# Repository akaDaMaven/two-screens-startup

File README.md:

Made and put together by DaMaven.
I'm not an native English speaker so please forgive me my grammar errors.

What does it do: This makes your desired app run on startup on two extended displays with two
 instances of the app each on its own display automaticaly. If you have more displays and want
 that app on all of them, I will show you how.

Use: I've done this for a restaurant that has two touchscreen monitors connected to one server
 (PC) with POS app that needed to be used from different locations without interfering.
 So if you need something like that, there it is.

Follow instuctions bellow:
--------------------------------
1.Download DisplayFusion from official DisplayFusion website (www.displayfusion.com)
	- This alows you to switch the app window inbetween all monitors no matter what side it is set on
	  in windows display settings. DisplayFusion has that on default to "CTRL+WindowsKey+X".

2.Install AutoHotkey_2.0.12_setup.exe OR download from official AutoHotkey website (www.autohotkey.com)
	- This alows the script to use hotkeys ( In our case it is the "CTRL+WindowsKey+X")
	  and convert .ahk file to .exe file. We want to convert .ahk file we create with AutoHotkey to .exe file
	  so we can run it on any PC that doesn't have AutoHotkey installed. To do that, open the Autohotkey Dash
	  and select "Compile". If that doesn't work install Ahk2Exe from Autohotkey folder in
	  "C:\Users\*USERNAME\AppData\Local\Programs\AutoHotkey\UX\install-ahk2exe.ahk". So once in Ahk2Exe is opened
	  in the Source browse path to your "AutoHotkeyScript.ahk" file, go to Base File under Options
	  and select your version of U64 AutoHotkey64.exe, if you have 32 bit system select U32 AutoHotkey32.exe.
	  Now click "Convert". Again you don't have to convert it if you have AutoHotkey installed.

IF you want to configure the hotkeys, edit the AutoHotkeyScript.ahk and go to the first line where it says
 "Send, #^x", search online for Autohotkey's documentation for Autohotkey Version 2.0 or go to
 "www.autohotkey.com/docs/v2/Hotkeys.htm". Once you know the hotkey shortcuts (#,^,!,etc.),
  type it after the "Send, {hotkeys}". Bare in mind that if you download a different version of AutoHotkey
  it does't have to work.

4.Edit the Autorun.ps1
	- First line - Change the path to where you have the application located.
	- Fourth line - (optional) Change the time after the app window moves to second screen.
	- Fifth line - Change the path to where you have the "AutoHotkeyScript.exe" located.

5.Create a shortcut for the "Autorun.ps1". Press "WindowsKey+R" and type in "shell:startup" (this opens Windows
 Startup folder). Copy the "Autorun.ps1" shortcut and copy it to the Windows Startup folder.

That's it!

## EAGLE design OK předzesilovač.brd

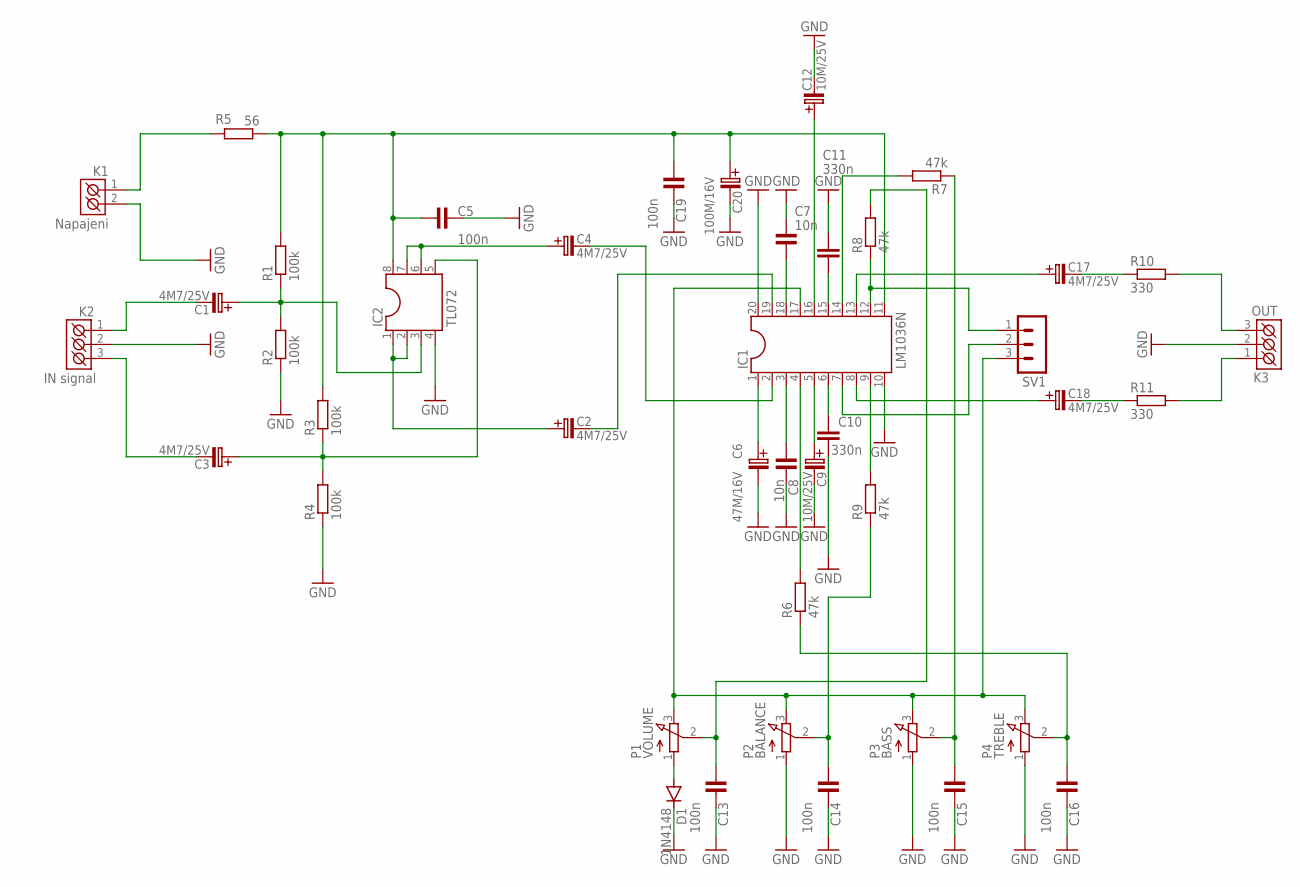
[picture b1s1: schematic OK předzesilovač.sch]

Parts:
C1, C2, C3, C4, C17, C18: 4M7/25V; C_EL_2
C5, C13, C14, C15, C16, C19: 100n; RM5_2,5
C6: 47M/16V; C_EL_2
C7, C8: 10n; RM5_2,5
C9, C12: 10M/25V; C_EL_2,5
C10, C11: 330n; C075-032X103
C20: 100M/16V; C_EL_3,5
D1: 1N4148; DO35-7
IC1: LM1036N; DIL20
IC2: TL072; DIL08
K1: Napajeni; ARK500/2
K2: IN signal; ARK500/3
K3: OUT; ARK500/3
P1: VOLUME; 3RP/1610N
P2: BALANCE; 3RP/1610N
P3: BASS; 3RP/1610N
P4: TREBLE; 3RP/1610N
R1: 100k; 0207/12
R2, R3, R4: 100k; 0204/7
R5: 56; 0204/7
R6, R7, R8, R9: 47k; 0207/12
R10: 330; 0204/7
R11: 330; 0207/12
SV1: MA03-1

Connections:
GND: C5.2, C6.C- (C_EL-), C7.1, C8.2, C9.C- (C_EL-), C10.2, C11.1, C12.C- (C_EL-), C13.2, C14.2, C15.2, C16.2, C19.2, C20.C- (C_EL-), D1.C, IC1.10, IC1.20, IC2.4, K1.2 (K2), K2.2 (K2), K3.2 (K2), P2.1 (A), P3.1 (A), P4.1 (A), R2.1, R4.1
unnamed: K3.1 (K1), R11.2
unnamed: K1.1 (K1), R5.2
unnamed: C1.C- (C_EL-), K2.1 (K1)
unnamed: C3.C+ (C_EL+), IC2.5, R3.1, R4.2
unnamed: C3.C- (C_EL-), K2.3 (K3)
unnamed: C4.C+ (C_EL+), IC2.6, IC2.7
unnamed: IC1.14, R7.2
unnamed: D1.A, P1.1 (A)
unnamed: C1.C+ (C_EL+), IC2.3, R1.1, R2.2
unnamed: C2.C+ (C_EL+), IC2.1, IC2.2
unnamed: C2.C- (C_EL-), IC1.19
unnamed: C4.C- (C_EL-), IC1.2
unnamed: C6.C+ (C_EL+), IC1.1
unnamed: C9.C+ (C_EL+), IC1.5
unnamed: C11.2, IC1.15
unnamed: C7.2, IC1.18
unnamed: C13.1, P1.2 (S), R8.2
unnamed: C14.1, P2.2 (S), R9.1
unnamed: C15.1, P3.2 (S), R7.1
unnamed: C16.1, P4.2 (S), R6.1
unnamed: IC1.7, SV1.2
unnamed: C12.C+ (C_EL+), IC1.16
unnamed: K3.3 (K3), R10.2
unnamed: C17.C- (C_EL-), R10.1
unnamed: C17.C+ (C_EL+), IC1.13
unnamed: IC1.17, P1.3 (E), P2.3 (E), P3.3 (E), P4.3 (E), SV1.3
unnamed: C10.1, IC1.6
unnamed: C18.C+ (C_EL+), IC1.8
unnamed: C18.C- (C_EL-), R11.1
unnamed: C8.1, IC1.3
unnamed: IC1.4, R6.2
unnamed: IC1.12, R8.1, SV1.1
unnamed: C5.1, C19.1, C20.C+ (C_EL+), IC1.11, IC2.8, R1.2, R3.2, R5.1
unnamed: IC1.9, R9.2

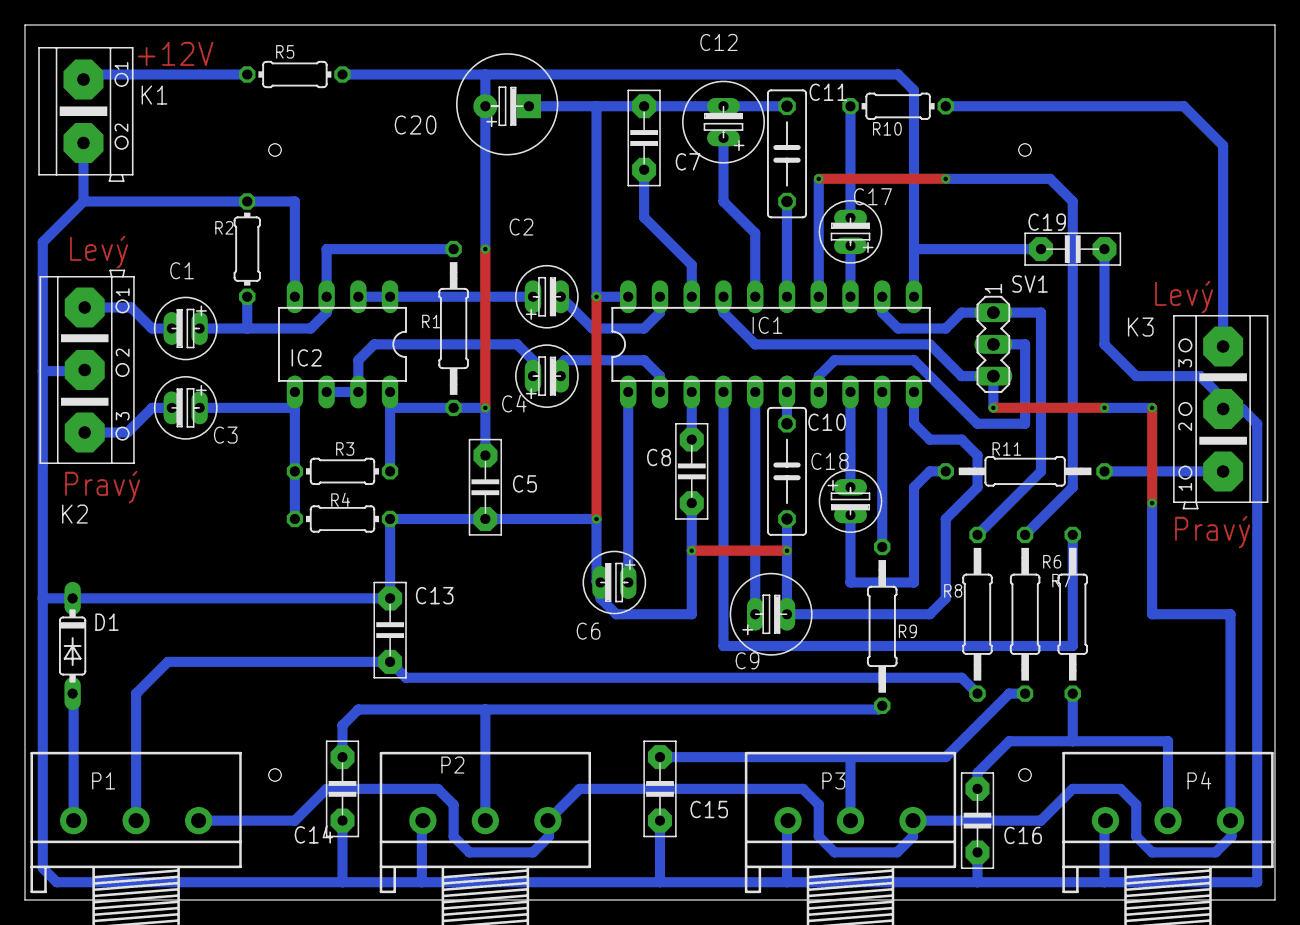
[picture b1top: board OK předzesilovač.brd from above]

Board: 2 copper layers, 100.0 x 70.0 mm, 42 parts (0 on the bottom side), 35 nets.

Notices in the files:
parts and their libraries:
Copyright (C) PaJa 2003-2009
Copyright (C) PaJa 2011-2014
